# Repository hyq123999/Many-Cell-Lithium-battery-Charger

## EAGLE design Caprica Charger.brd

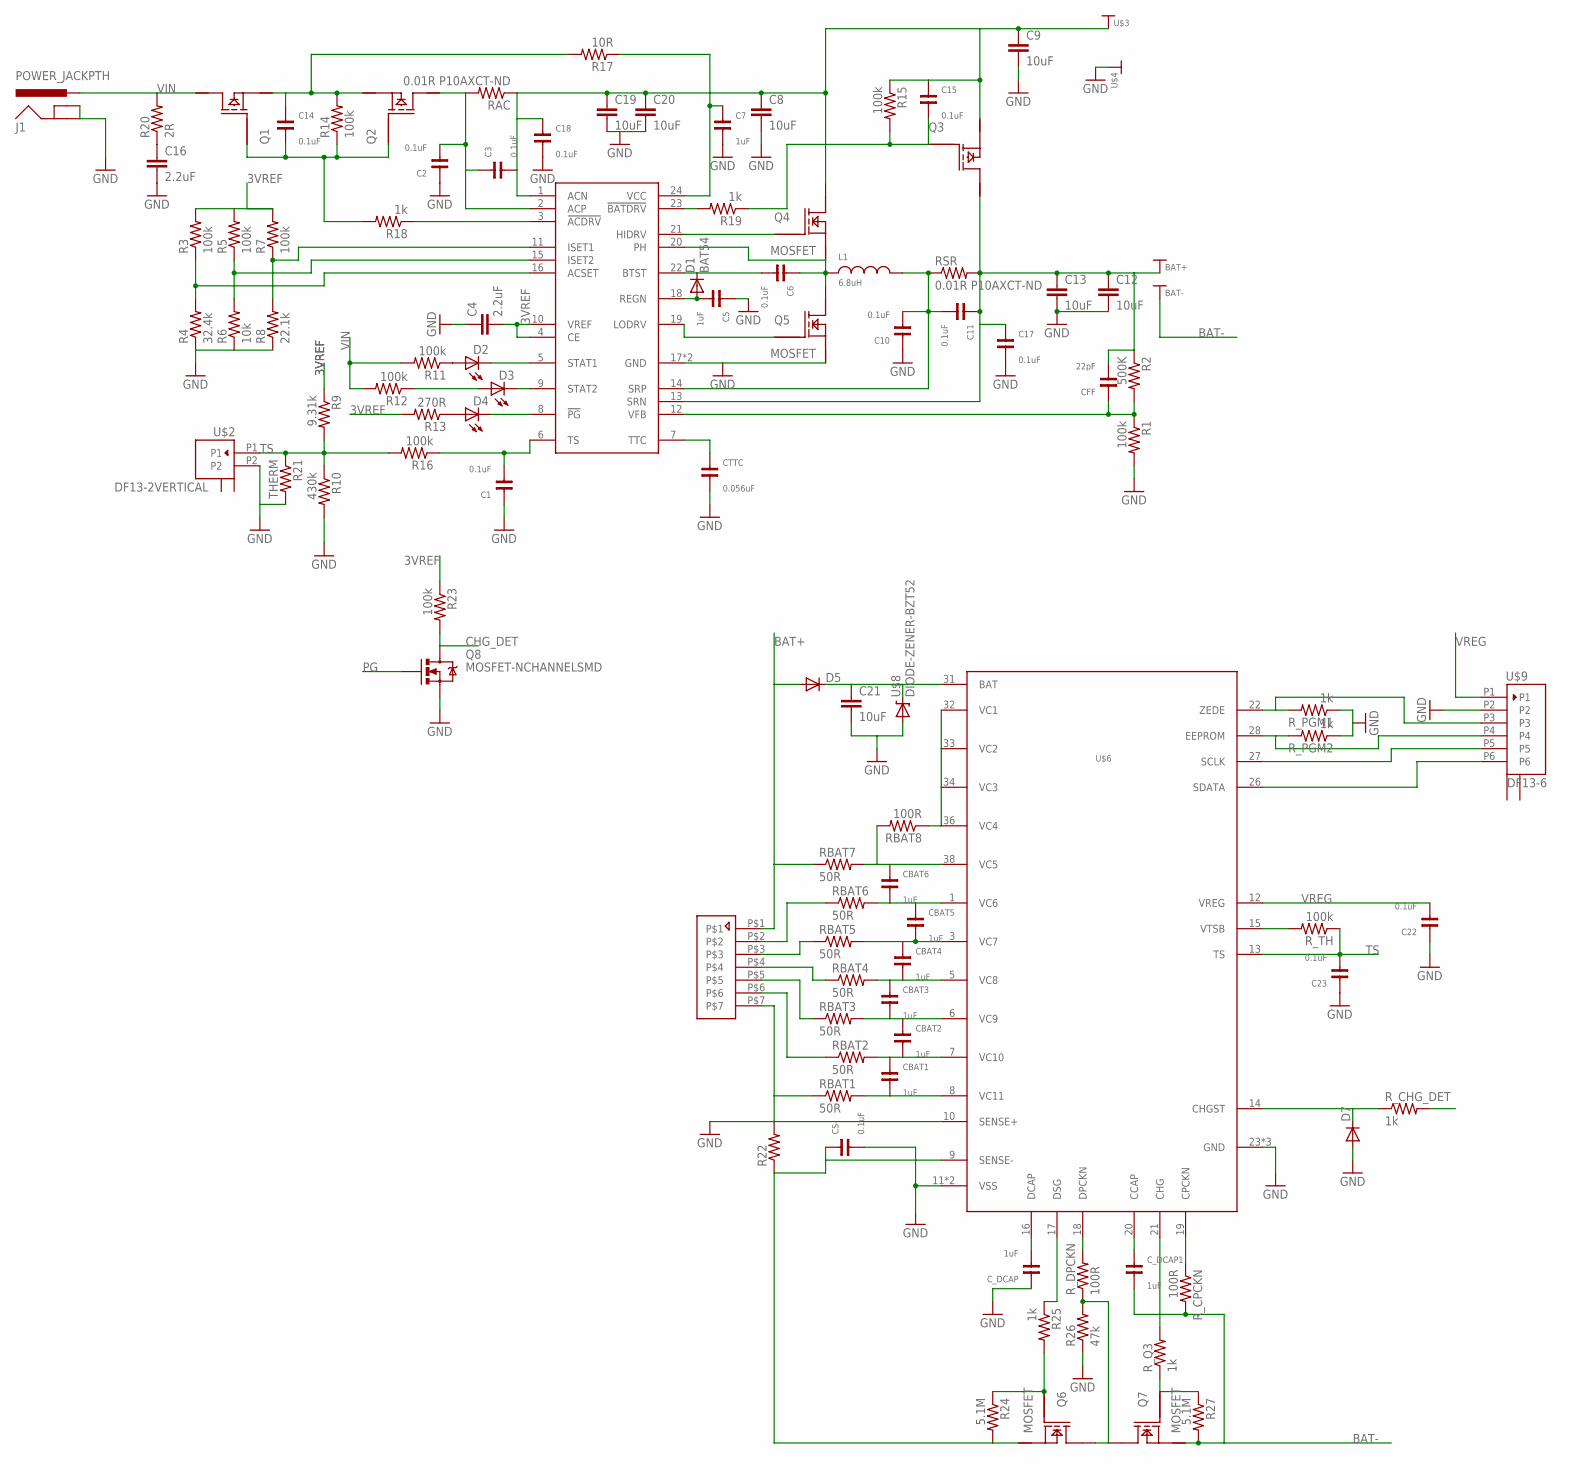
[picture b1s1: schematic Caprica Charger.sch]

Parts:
BAT+: HIGHCURRENTPAD2; HIGH_CURRENT_PAD2
BAT-: HIGHCURRENTPAD2; HIGH_CURRENT_PAD2
C1, C2, C3, C6, C10, C11, C14, C15, C17, C18, C22, C23: 0.1uF; 0603-CAP
C4, C16: 2.2uF; 1206
C5, C7: 1uF; 0603-CAP
C8, C9, C12, C13, C19, C20, C21: 10uF; 1206
CBAT1, CBAT2, CBAT3, CBAT4, CBAT5, CBAT6: 1uF; 0603-CAP
CFF: 22pF; 0603-CAP
CS-: 0.1uF; 0603-CAP
CTTC: 0.056uF; 0603-CAP
C_DCAP, C_DCAP1: 1uF; 0603-CAP
D1: BAT54; SOT23-3
D2, D3, D4: LED1206; LED-1206
D5: DIODESMA; SMA-DIODE
D7: DIODESOD; SOD-323
J1: POWER_JACKPTH; POWER_JACK_PTH
L1: 6.8uH; SDR0403_INDUCTOR
Q1, Q2, Q3: MOSFET_PCH; POWERPAK_1212-8
Q4, Q5, Q6, Q7: MOSFET; POWERPAK_1212-8
Q8: MOSFET-NCHANNELSMD; SOT23-3
R1, R3, R5, R7, R11, R12, R14, R15, R16, R23: 100k; 0603-RES
R2: 500K; 0603-RES
R4: 32.4k; 0603-RES
R6: 10k; 0603-RES
R8: 22.1k; 0603-RES
R9: 9.31k; 0603-RES
R10: 430k; 0603-RES
R13: 270R; 0603-RES
R17: 10R; 0603-RES
R18, R19, R25: 1k; 0603-RES
R20: 2R; 0603-RES
R21: THERM; 0603-RES
R22: RESISTOROHMITE; OHMITE_FCSL64_CURRENT_SENSE_RESISTOR
R24, R27: 5.1M; 0603-RES
R26: 47k; 0603-RES
RAC: 0.01R P10AXCT-ND; 0603-RES
RBAT1, RBAT2, RBAT3, RBAT4, RBAT5, RBAT6, RBAT7: 50R; 0603-RES
RBAT8: 100R; 0603-RES
RSR: 0.01R P10AXCT-ND; 0603-RES
R_CHG_DET: 1k; 0603-RES
R_CPCKN: 100R; 0603-RES
R_DPCKN: 100R; 0603-RES
R_PGM1, R_PGM2: 1k; 0603-RES
R_Q3: 1k; 0603-RES
R_TH: 100k; 0603-RES
U$1: BQ24610_LIPO_CHARGER; QFN-24_ALT2
U$2: DF13-2VERTICAL; DF13-2-VERT
U$3, U$4: HIGHCURRENTPAD2; HIGH_CURRENT_PAD2
U$6: BQ77910A_BATTERY_PROTECTOR; TSSOP38
U$7: JST_XH_7; B7B-XH
U$8: DIODE-ZENER-BZT52; SOD-323
U$9: DF13-6; DF13-6-VERT

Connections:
3VREF: C4.2, R3.2, R5.2, R7.2, R9.1, R13.2, R23.1, U$1.4 (CE), U$1.10 (VREF)
BAT+: BAT+.P$1, C11.1, C12.1, C13.1, C17.1, CFF.2, D5.A, Q3.P5 (DRAIN), Q3.P6 (DRAIN), Q3.P7 (DRAIN), Q3.P8 (DRAIN), Q3.PAD (DRAIN), R2.1, RBAT7.1, RSR.2, U$1.13 (SRN), U$7.P$1
BAT-: BAT-.P$1, C_DCAP1.2, Q7.P1 (S), Q7.P2 (S), Q7.P3 (S), R27.2, R_CPCKN.2
CHG_DET: Q8.3 (D), R23.2, R_CHG_DET.2
GND: C1.1, C2.1, C4.1, C5.1, C7.2, C8.2, C9.2, C10.1, C12.2, C13.2, C16.2, C17.2, C18.2, C19.2, C20.2, C21.2, C22.1, C23.1, CS-.2, CTTC.2, C_DCAP.1, D7.2 (A), J1.GND, J1.GNDBREAK, Q5.P1 (S), Q5.P2 (S), Q5.P3 (S), Q8.2 (S), R1.2, R4.1, R6.1, R8.1, R10.2, R21.2, R22.P$2 (2), R26.1, RBAT1.1, R_PGM1.1, R_PGM2.1, U$1.17 (GND), U$1.EP (GND), U$2.P2, U$4.P$1, U$6.10 (SENSE+), U$6.11 (VSS), U$6.23 (GND), U$6.24 (GND), U$6.25 (GND), U$6.29 (VSS), U$7.P$7, U$8.2 (A), U$9.P2
HIDRV: Q4.P4 (G), U$1.21 (HIDRV)
unnamed: D2.A, R11.1
unnamed: C14.1, Q1.P1 (SOURCE), Q1.P2 (SOURCE), Q1.P3 (SOURCE), Q2.P1 (SOURCE), Q2.P2 (SOURCE), Q2.P3 (SOURCE), R14.2, R17.2
unnamed: C14.2, Q1.P4 (GATE), Q2.P4 (GATE), R14.1, R18.2
unnamed: C2.2, C3.1, Q2.P5 (DRAIN), Q2.P6 (DRAIN), Q2.P7 (DRAIN), Q2.P8 (DRAIN), Q2.PAD (DRAIN), RAC.2, U$1.2 (ACP)
unnamed: CBAT1.1, CBAT2.2, RBAT2.2, U$6.7 (VC10)
unnamed: R18.1, U$1.3 (!ACDRV!)
unnamed: C16.1, R20.1
unnamed: C7.1, R17.1, U$1.24 (VCC)
unnamed: R5.1, R6.2, U$1.15 (ISET2)
unnamed: D2.C, U$1.5 (STAT1)
unnamed: D3.C, U$1.9 (STAT2)
unnamed: R25.1, U$6.17 (DSG)
unnamed: D3.A, R12.1
unnamed: D4.A, R13.1
unnamed: R3.1, R4.2, U$1.16 (ACSET)
unnamed: R7.1, R8.2, U$1.11 (ISET1)
unnamed: CBAT2.1, CBAT3.2, RBAT3.2, U$6.6 (VC9)
unnamed: C1.2, R16.1, U$1.6 (TS)
unnamed: CTTC.1, U$1.7 (TTC)
unnamed: R19.2, U$1.23 (!BATDRV!)
unnamed: C15.2, Q3.P4 (GATE), R15.2, R19.1
unnamed: CBAT3.1, CBAT4.2, RBAT4.2, U$6.5 (VC8)
unnamed: CBAT1.2, RBAT1.2, U$6.8 (VC11)
unnamed: C6.1, L1.P$1, Q4.P1 (S), Q4.P2 (S), Q4.P3 (S), Q5.P5 (D), Q5.P6 (D), Q5.P7 (D), Q5.P8 (D), Q5.PAD (D), U$1.20 (PH)
unnamed: C10.2, C11.2, L1.P$2, RSR.1, U$1.14 (SRP)
unnamed: C6.2, D1.3 (C), U$1.22 (BTST)
unnamed: C5.2, D1.1 (A), U$1.18 (REGN)
unnamed: Q5.P4 (G), U$1.19 (LODRV)
unnamed: CBAT5.1, CBAT6.2, RBAT6.2, U$6.1 (VC6)
unnamed: CFF.1, R1.1, R2.2, U$1.12 (VFB)
unnamed: CBAT4.1, CBAT5.2, RBAT5.2, U$6.3 (VC7)
unnamed: C_DCAP.2, U$6.16 (DCAP)
unnamed: CBAT6.1, RBAT7.2, RBAT8.2, U$6.38 (VC5)
unnamed: RBAT8.1, U$6.32 (VC1), U$6.33 (VC2), U$6.34 (VC3), U$6.36 (VC4)
unnamed: C21.1, D5.C, U$6.31 (BAT), U$8.1 (C)
unnamed: D7.1 (C), R_CHG_DET.1, U$6.14 (CHGST)
unnamed: RBAT2.1, U$7.P$6
unnamed: RBAT3.1, U$7.P$5
unnamed: RBAT4.1, U$7.P$4
unnamed: Q6.P4 (G), R24.1, R25.2
unnamed: RBAT6.1, U$7.P$2
unnamed: RBAT5.1, U$7.P$3
unnamed: R_DPCKN.2, U$6.18 (DPCKN)
unnamed: Q6.P5 (D), Q6.P6 (D), Q6.P7 (D), Q6.P8 (D), Q6.PAD (D), Q7.P5 (D), Q7.P6 (D), Q7.P7 (D), Q7.P8 (D), Q7.PAD (D), R26.2, R_DPCKN.1
unnamed: U$6.27 (SCLK), U$9.P5
unnamed: CS-.1, Q6.P1 (S), Q6.P2 (S), Q6.P3 (S), R22.P$1 (1), R24.2, U$6.9 (SENSE-)
unnamed: C_DCAP1.1, U$6.20 (CCAP)
unnamed: R_Q3.2, U$6.21 (CHG)
unnamed: Q7.P4 (G), R27.1, R_Q3.1
unnamed: U$6.26 (SDATA), U$9.P6
unnamed: R_CPCKN.1, U$6.19 (CPCKN)
unnamed: R_PGM2.2, U$6.28 (EEPROM), U$9.P4
unnamed: R_TH.2, U$6.15 (VTSB)
unnamed: R_PGM1.2, U$6.22 (ZEDE), U$9.P3
PG: D4.C, Q8.1 (G), U$1.8 (!PG!)
SYS+: C3.2, C8.1, C9.1, C15.1, C18.1, C19.1, C20.1, Q3.P1 (SOURCE), Q3.P2 (SOURCE), Q3.P3 (SOURCE), Q4.P5 (D), Q4.P6 (D), Q4.P7 (D), Q4.P8 (D), Q4.PAD (D), R15.1, RAC.1, U$1.1 (ACN), U$3.P$1
TS: C23.2, R9.2, R10.1, R16.2, R21.1, R_TH.1, U$2.P1, U$6.13 (TS)
VIN: J1.PWR, Q1.P5 (DRAIN), Q1.P6 (DRAIN), Q1.P7 (DRAIN), Q1.P8 (DRAIN), Q1.PAD (DRAIN), R11.2, R12.2, R20.2
VREG: C22.2, U$6.12 (VREG), U$9.P1

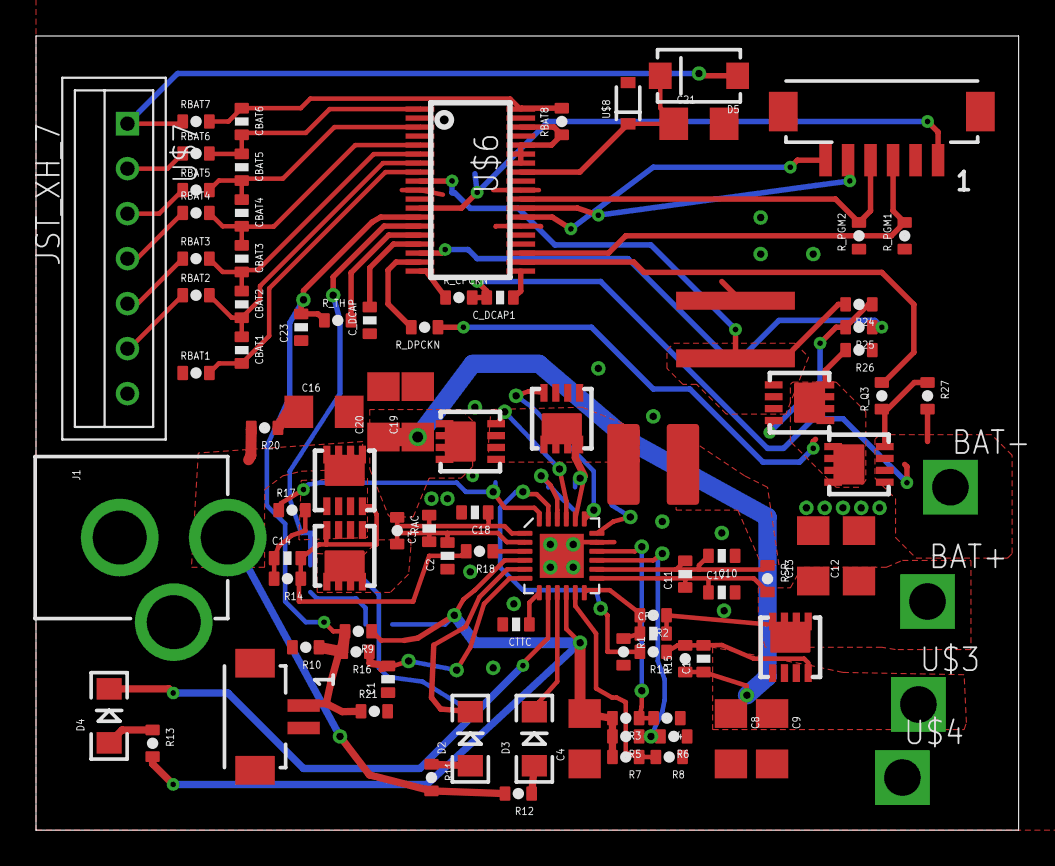
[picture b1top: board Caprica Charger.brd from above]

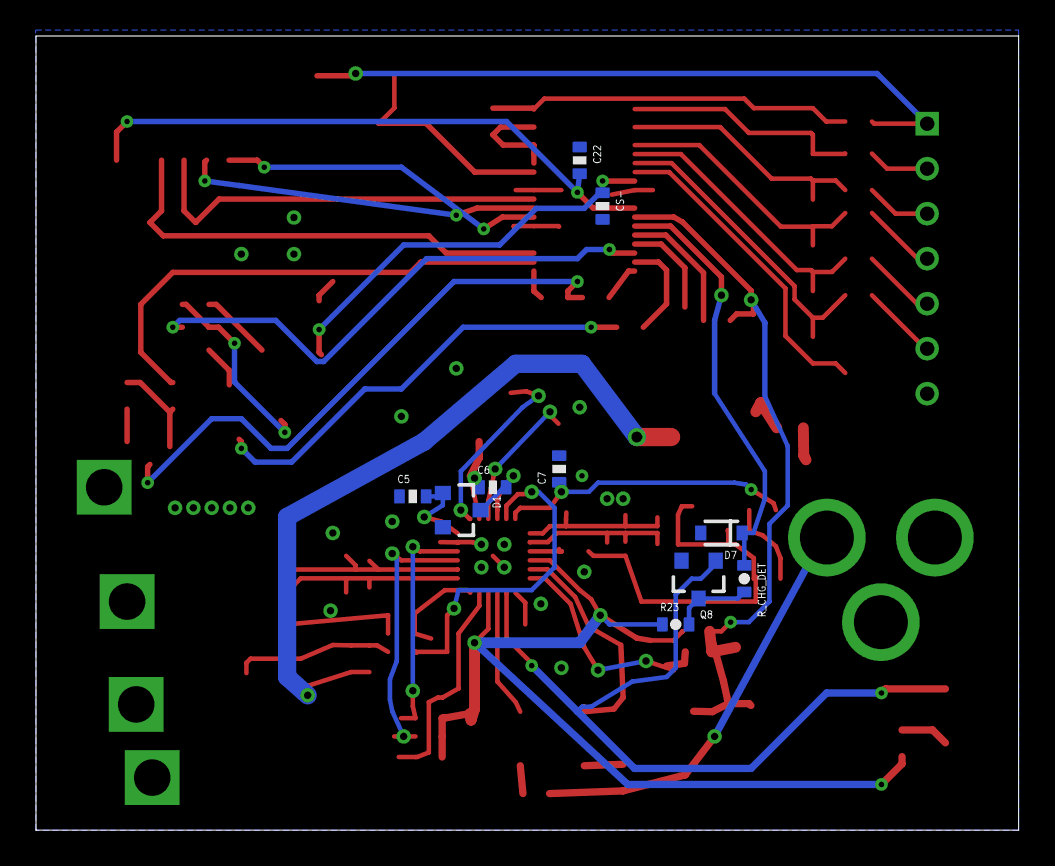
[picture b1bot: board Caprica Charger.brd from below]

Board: 2 copper layers, 54.6 x 44.1 mm, 104 parts (10 on the bottom side), 65 nets.

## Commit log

2012-12-17 Initial Commit. Basic schematic and board layout. Nothing AT ALL has been checked.
2012-12-18 Everything patched together
2012-12-24 Balancing added and all laid out. Still may be all wrong.
2012-12-24 Add gitignore for damn .DS_Store files

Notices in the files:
parts and their libraries:
SparkFun: Licensing: CC v3.0 Share-Alike You are welcome to use this library for commercial purposes.
